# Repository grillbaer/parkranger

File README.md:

# parkranger
Ultrasonic park distance LED lights for garage or carport.

Feel free to use this project as a base for your own projects AT YOUR OWN RISK!

## Hardware

AVR micro-controller ATmega ATtiny84
 - internal oscillator at 8.0 MHz (disable fuse CLKDIV8!)
 
Ultrasonic sensor module HC-SR04
 - trigger on PA0 (SOIC pin 13)
 - echo on PA1/PCINT1 (SOIC pin 12)

RGB LED
 - 20 mA LEDs or 12V LED module without resistor, both with common anode
 - red on PA5 (SOIC pin 8)
 - green on PA6 (SOIC pin 7)
 - blue on PA7 (SOIC pin 6)

## Software

C code for Atmel Studio 7.0
 - main loop triggers measurements
 - different LED colors/brightness using PWM signals from timer0 and timer1
 - timer0 overflows are counted using interrupt until echo is received to calculate distance
 - echo signal triggers interrupt PCINT1 to start/stop duration counting
 - switches between standby mode (LED almost off, 500ms between measurements, after 60 seconds without distance changes) and parking mode (LED shows distance, 100ms between measurements, after distance changes)

## Electronic CAD files

Design files are made with KiCad. Gerber files for PCB production have also been generated.

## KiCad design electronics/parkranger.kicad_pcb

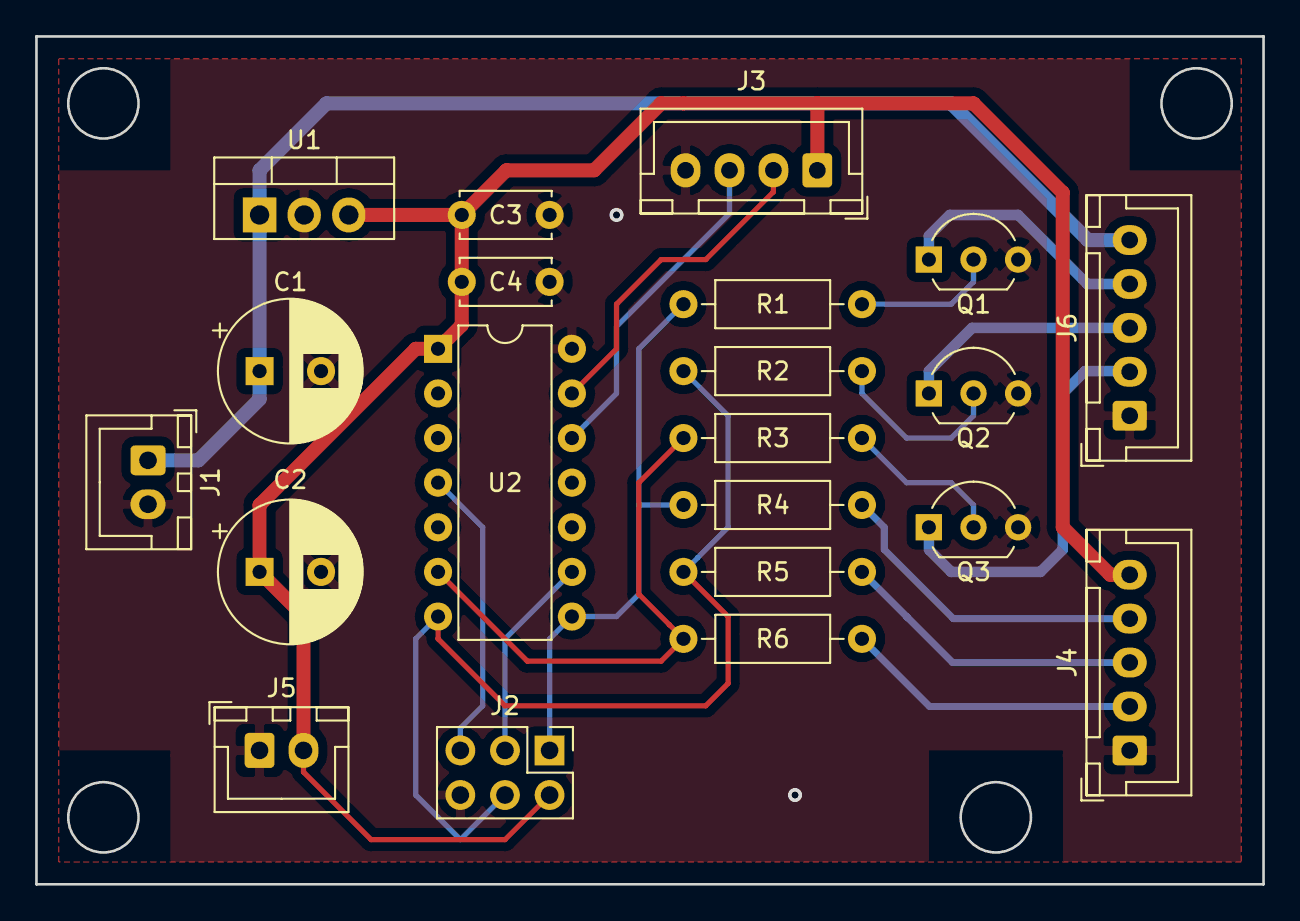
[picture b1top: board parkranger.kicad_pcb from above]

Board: 2 copper layers, 69.8 x 48.3 mm, 21 parts (0 on the bottom side), 19 nets.

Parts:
C1, C2: 100µ; CP_Radial_D8.0mm_P3.50mm
C3, C4: 100n; C_Disc_D5.0mm_W2.5mm_P5.00mm
J1: VCC in GND-12V; JST_XH_B02B-XH-A_1x02_P2.50mm_Vertical
J2: AVR-ISP; PinHeader_2x03_P2.54mm_Vertical
J3: HC-SR04 GND-Ec-Tr-5V; JST_XH_B04B-XH-A_1x04_P2.50mm_Vertical
J4: (GND)-B-G-R-A LED; JST_XH_B05B-XH-A_1x05_P2.50mm_Vertical
J5: GND-5V out; JST_XH_B02B-XH-A_1x02_P2.50mm_Vertical
J6: (GND)-B-G-R-12V; JST_XH_B05B-XH-A_1x05_P2.50mm_Vertical
Q1, Q2, Q3: BC337-40; TO-92L_Inline_Wide
R1, R2, R3: 2K2; R_Axial_DIN0207_L6.3mm_D2.5mm_P10.16mm_Horizontal
R4: 150; R_Axial_DIN0207_L6.3mm_D2.5mm_P10.16mm_Horizontal
R5, R6: 120; R_Axial_DIN0207_L6.3mm_D2.5mm_P10.16mm_Horizontal
U1: LM7805; TO-220-3_Vertical
U2: ATtiny84; DIP-14_W7.62mm

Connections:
+5V: C2.1, C3.2, C4.2, J2.2, J3.1, J4.5, J5.2, U1.3, U2.1
+12V: C1.1, J1.1, J6.5, U1.1
GND: C1.2, C2.2, C3.1, C4.1, J1.2, J2.6, J3.4, J4.1, J5.1, J6.1, Q1.3, Q2.3, Q3.3, U1.2, U2.14
unnamed: J2.1, R1.2, R4.2, U2.8
unnamed: J2.3, U2.9
unnamed: J2.4, R2.2, R5.2, U2.7
unnamed: J2.5, U2.4
unnamed: J3.2, U2.13
unnamed: J3.3, U2.12
unnamed: J4.2, R6.1
unnamed: J4.3, R5.1
unnamed: J4.4, R4.1
unnamed: J6.2, Q3.1
unnamed: J6.3, Q2.1
unnamed: J6.4, Q1.1
unnamed: Q1.2, R1.1
unnamed: Q2.2, R2.1
unnamed: Q3.2, R3.1
unnamed: R3.2, R6.2, U2.6

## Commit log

2019-02-03 Initial release
2019-02-03 added .gitignore
2019-02-03 Create LICENSE
2019-02-07 added KiCad schematics and PCB, moved to subfolders
2019-02-10 changed LEDs to 12V high is on, added blinking for short distances
2019-02-16 adjusted ranges
2019-02-16 added video and moved some images
2019-02-16 added youtube video thumbnail
